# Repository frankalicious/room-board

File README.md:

room-board-schematic
====================
# hardware
- MSP430G2553IN20
- pir module
- brightness measuring with led (kicad version uses phototransistor)
- nrf24l01 radio module

# gateway
https://github.com/frankalicious/nrf24l01-serial-gateway

# old schematic
gschem was used for first schematic version

# current schematic and board
designed in kicad

# git submodule
msp430-gcc firmware uses msprf24
```bash
$ git submodule init
$ git submodule update
```
For more information about git submodules see here: http://git-scm.com/book/en/v2/Git-Tools-Submodules

Use firmware/msp430-gcc/.
firmware/Enrf24_TXdemo_with_PIR/ does not seem to work

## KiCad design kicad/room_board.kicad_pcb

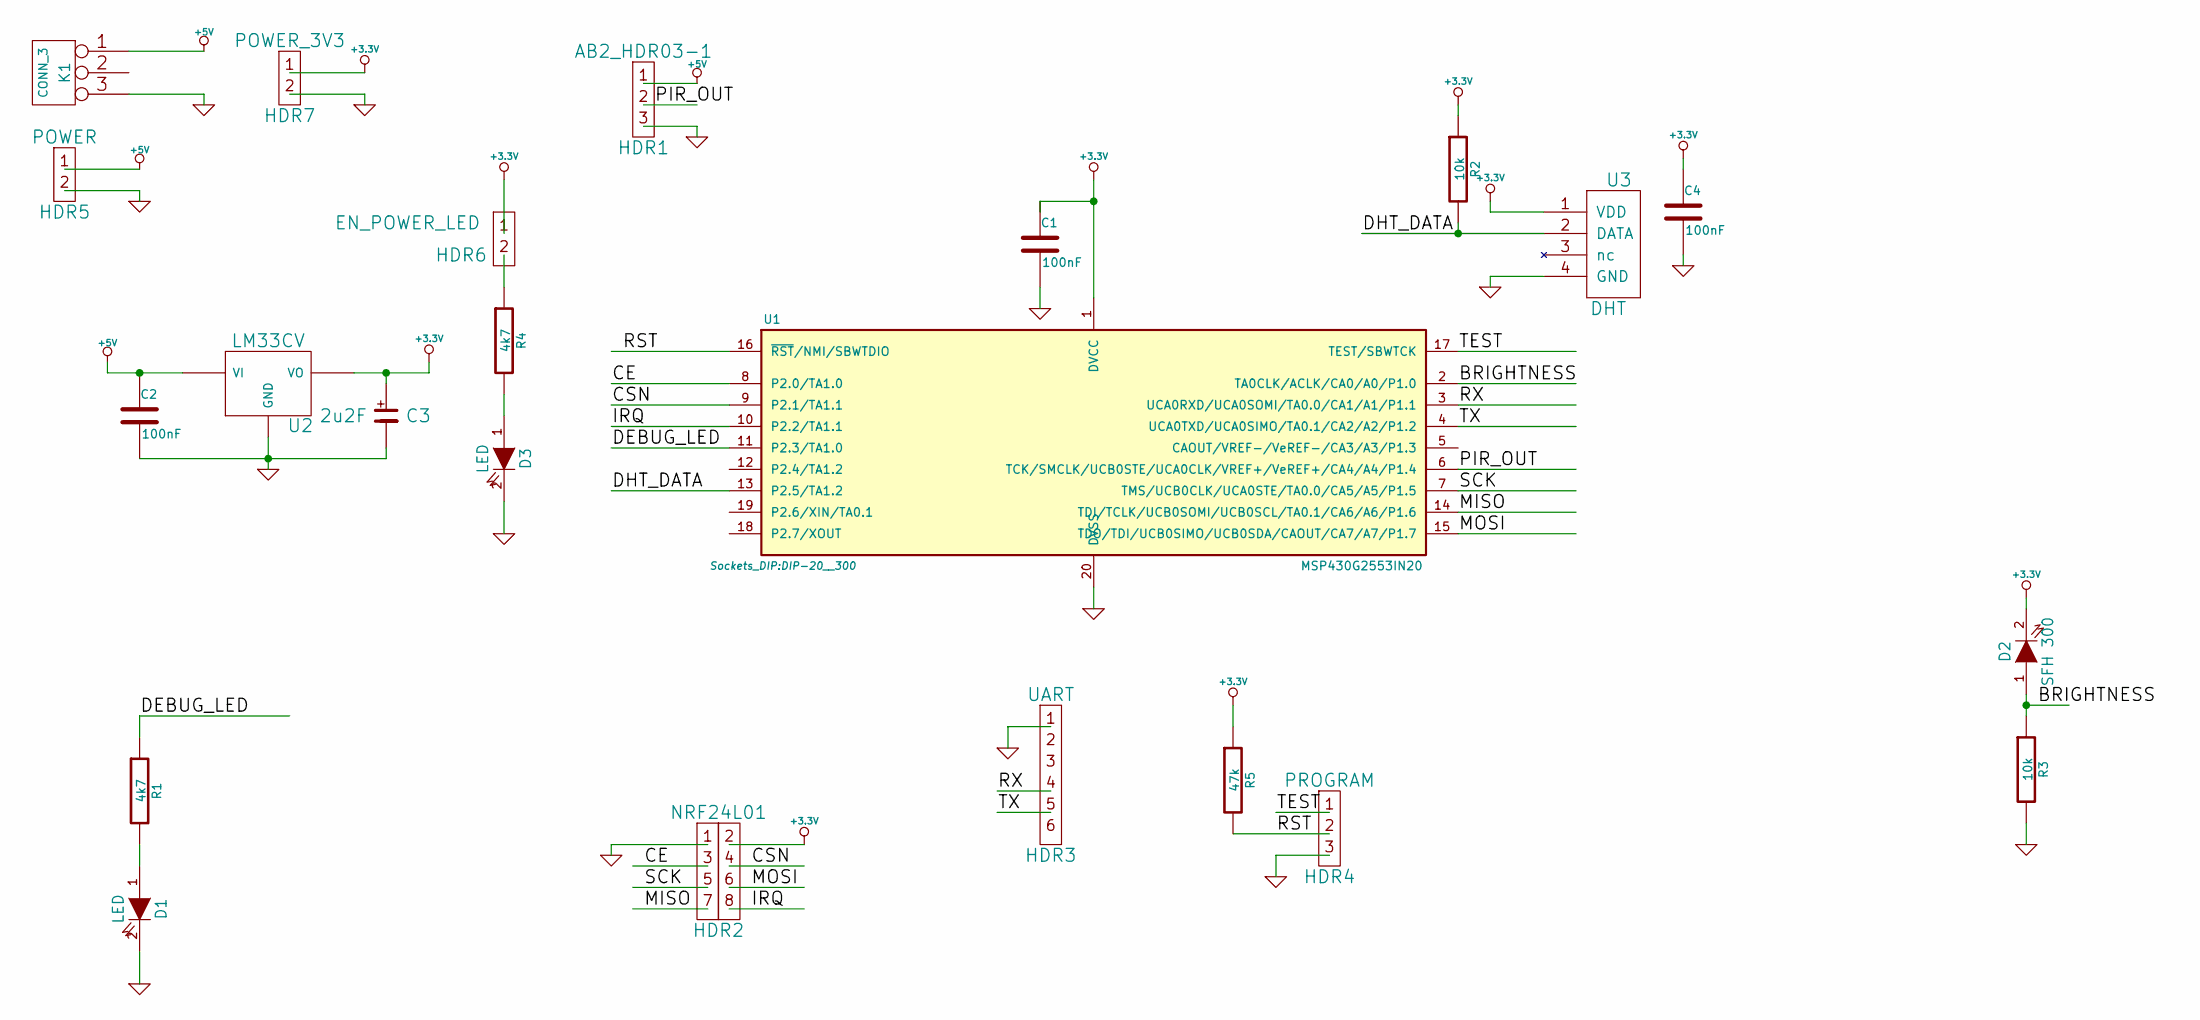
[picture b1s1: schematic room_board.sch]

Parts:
C1, C2, C4: 100nF; C1
C3: 2u2F; Elko_vert_11x5mm_RM2.5
D1, D3: LED; LED-5MM
D2: SFH 300; LED-5MM
HDR1: AB2_HDR03-1; AB2_HDR_M03-1V
HDR2: NRF24L01; AB2_HDR_M04-2V
HDR3: UART; AB2_HDR_M06-1V
HDR4: PROGRAM; AB2_HDR_M03-1V
HDR5: POWER; AB2_HDR_M02-1V
HDR6: EN_POWER_LED; AB2_HDR_M02-1V
HDR7: POWER_3V3; AB2_HDR_M02-1V
K1: CONN_3; AB2_PB_2MM_JACK_PTH
R1, R4: 4k7; R3
R2, R3: 10k; R3
R5: 47k; R3
U1: MSP430G2553IN20; DIP-20__300
U2: LM33CV; LM78XXV
U3: DHT; Pin_Header_Straight_1x04

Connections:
+3.3V: C1.1, C3.1 (A), C4.1, D2.2 (K), HDR2.2, HDR6.1, HDR7.1, R2.1, R5.1, U1.1 (DVCC), U2.VO, U3.1 (VDD)
+5V: C2.1, HDR1.1, HDR5.1, K1.1, U2.VI
/BRIGHTNESS: D2.1 (A), R3.1, U1.2 (TA0CLK/ACLK/CA0/A0/P1.0)
/CE: HDR2.3, U1.8 (P2.0/TA1.0)
/CSN: HDR2.4, U1.9 (P2.1/TA1.1)
/DEBUG_LED: R1.1, U1.11 (P2.3/TA1.0)
/DHT_DATA: R2.2, U1.13 (P2.5/TA1.2), U3.2 (DATA)
/IRQ: HDR2.8, U1.10 (P2.2/TA1.1)
/MISO: HDR2.7, U1.14 (TDI/TCLK/UCB0SOMI/UCB0SCL/TA0.1/CA6/A6/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)
/MOSI: HDR2.6, U1.15 (TDO/TDI/UCB0SIMO/UCB0SDA/CAOUT/CA7/A7/P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)
/PIR_OUT: HDR1.2, U1.6 (TCK/SMCLK/UCB0STE/UCA0CLK/VREF+/VeREF+/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)
/RST: HDR4.2, R5.2, U1.16 (~RST~/NMI/SBWTDIO)
/RX: HDR3.4, U1.3 (UCA0RXD/UCA0SOMI/TA0.0/CA1/A1/P1.1)
/SCK: HDR2.5, U1.7 (TMS/UCB0CLK/UCA0STE/TA0.0/CA5/A5/P1.5)
/TEST: HDR4.1, U1.17 (TEST/SBWTCK)
/TX: HDR3.5, U1.4 (UCA0TXD/UCA0SIMO/TA0.1/CA2/A2/P1.2)
GND: C1.2, C2.2, C3.2 (K), C4.2, D1.2 (K), D3.2 (K), HDR1.3, HDR2.1, HDR3.1, HDR4.3, HDR5.2, HDR7.2, K1.3, R3.2, U1.20 (DVSS), U2.GND, U3.4 (GND)
unnamed: D1.1 (A), R1.2
unnamed: D3.1 (A), R4.2
unnamed: HDR6.2, R4.1

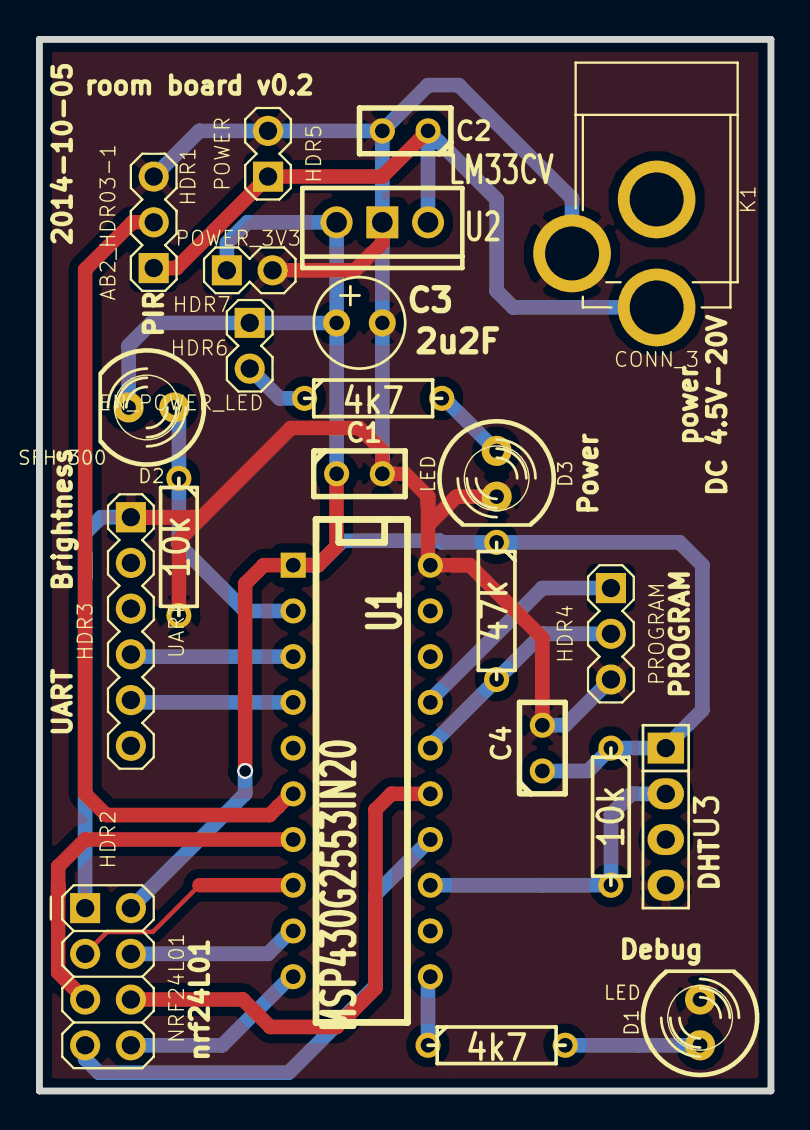
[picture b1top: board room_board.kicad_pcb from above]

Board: 2 copper layers, 40.6 x 58.4 mm, 23 parts (0 on the bottom side), 20 nets.

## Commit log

2013-12-17 add preliminary schematic
2013-12-17 add some info in README
2013-12-17 move schematic to subdirectory
2013-12-17 add firmware
    Firmware uses Energia and the Enrf24 library
2014-01-05 update schematic
    - add most of the components
2014-01-05 update firmware
    - add temperaturemeassurement
2014-01-05 add preliminary pcb
2014-01-05 add picture of schematic
2014-01-05 add diagram
2014-02-23 add parenthesis because of compiler warning
2014-02-23 always measure brightness
    test if program still works if brightness is also measured when lights are turned on
2014-02-23 remove unused old code
2014-02-23 split functions in endless loop
    seperate in create_string, print_string ans send string
2014-02-23 exchange MOSI and MISO on nrf24L01+
    They have been swapped.
2014-02-23 fix parenthesis from commit 6f576f7
    Silly me set the parenthesis wrong which lends to wrong temperature values.
2014-10-04 add kicad files
    2 layer board
2014-10-04 Update README.md
    update readme for kicad changes
2014-10-04 Update README.md
    changed microcontroller
2014-10-05 update files sent to osh park for board creation
2014-11-07 add wip msp430 gcc version for osh park version
2014-11-07 add msprf24
    Add nrf24l01 library msprf24 as submodule msprf24
2014-11-07 add check if temperature should be measured in ernergia sketch
2014-11-07 update MSP430 version in readme
2014-11-07 add preliminary gitignore file
2014-11-07 update kicad schematic
2014-11-07 change node number in energia sketch
2014-11-07 schematic: add todo to change c3
    According to the datasheet of the lm33cv c3 has to be an electrolyt capacitor and not a default capacitor.
2014-11-09 add gdb makefile target and gdbinit file
2014-11-09 move submodules to subfolders (adc/uart/etc) and adjust makefile
2014-11-09 fix gdbinit name
2014-11-09 fix indenting in the makefile
    Remove the unnecessary spaces.
2014-11-09 add helper macro to toggle debug led
2014-11-09 measure adc value
    For now without interrupt because the interrupt did not work.
2014-11-09 fix include of header files
    The modules were moved to subdirectories.
    Therefore the including in the main file have to be fixed.
2014-11-09 remove unused line in uart module
    Because of the comment style there was a warning.
2014-11-09 add code for dht11 temperature and humidity measuring
    Add dht11 code from https://github.com/bafeigum/DHT11-Library-for-MSP430.
    Changed the comments from // to /*. Otherwise there are a a lot of gcc warnings with the settings in the makefile.
2014-11-09 init msp430 clock
    To get a stable msp430 clock for uart initialize the clock.
2014-11-09 add delay_ms function
    We have a 1 Mhz clock. So we need 1000 cpu cycles for 1 ms.
2014-11-09 extend output on serial port
    Add info about measured variable.
2014-11-09 move adc non intterupt version to adc module
2014-11-09 fix adc interrupt service routine
    The pragma for the irq was missing.
2014-11-09 use interrupt version of adc
2014-11-09 fix gateway
    Remove wrong gateway file from project. This was not a gateway at all.
    Add link to github gateway project.
2014-11-09 fix comment style in energia sketch
2014-11-14 wip msp430 nrf24l01
    does not work
2014-11-14 update msprf24
    - replace all the comments
2014-11-14 remove inappropriate payload
2014-11-14 fix spelling error
2014-11-14 fix setting of nrf24l01 baudrate and power
    Set the nrf24l01 baudrate to the same as the receiver.
    Also set the power to max.
2014-11-14 Get the transmit working
    Remove the tx flush.
    This was added for testing but does not send at all.
2014-11-14 remove the unused commented nrf24l01 settings
2014-11-14 add humidity to nrf24l01 payload
2014-12-01 add used symbols in schematic
    The symbols are in the cache library in the project path.
2014-12-06 add jumper for power led
    Enable possibility to turn off power led to reduce power consumption when using a battery.
2014-12-06 move dht to border
    The former position of the DHT was under the nrf24l01.
    Fixes #4.
2014-12-06 replace capacitory with electrolytic version
    The LCV33CV needs an electrolytic capacitor on it's output.
    Fix in schematic and pcb.
2014-12-08 update schematic/layout
    - replace LM7805 symbol with LM33CV in schematic and layout
    - add 3.3V power connector in schematic and layout
    - replace 3pin uart with 6pin. only in schematic not done yet in layout
2014-12-08 fix layout of uart connector
2017-02-18 add info about latest firmware version
